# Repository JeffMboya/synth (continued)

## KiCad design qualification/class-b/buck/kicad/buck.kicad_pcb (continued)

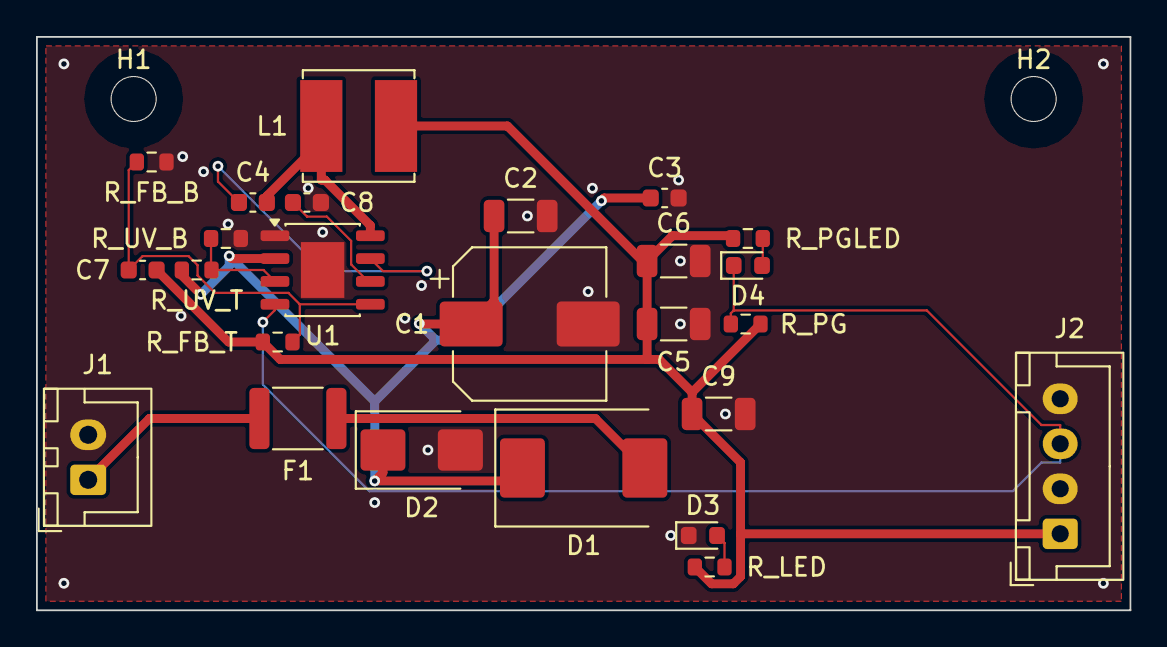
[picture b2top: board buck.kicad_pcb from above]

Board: 4 copper layers, 60.8 x 31.9 mm, 27 parts (0 on the bottom side), 13 nets.

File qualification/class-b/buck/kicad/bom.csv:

refdes,value,kind,description,kicad_symbol,kicad_footprint,lcsc_pn,mpn
C1,47uF,capacitor,"Honor Elec RVT1H470M0810, 47 uF 50 V +/-20 % 105 C SMD aluminium electrolytic, 8 mm diameter x 10.2 mm, polarised (pin 1 is +); JLCPCB C2895739",Device:C_Polarized,Capacitor_SMD:CP_Elec_8x10,,RVT1H470M0810
C2,10uF,capacitor,"Generic 1206 ceramic capacitor, any value",Device:C,Capacitor_SMD:C_1206_3216Metric,,
C3,220nF,capacitor,"Generic 0603 MLCC, X7R/X5R, any value",Device:C,Capacitor_SMD:C_0603_1608Metric,,
C4,100nF,capacitor,"Generic 0603 MLCC, X7R/X5R, any value",Device:C,Capacitor_SMD:C_0603_1608Metric,,
C5,22uF,capacitor,"Generic 1206 ceramic capacitor, any value",Device:C,Capacitor_SMD:C_1206_3216Metric,,
C6,22uF,capacitor,"Generic 1206 ceramic capacitor, any value",Device:C,Capacitor_SMD:C_1206_3216Metric,,
C7,56pF,capacitor,"Generic 0603 MLCC, X7R/X5R, any value",Device:C,Capacitor_SMD:C_0603_1608Metric,,
C8,1uF,capacitor,"Generic 0603 MLCC, X7R/X5R, any value",Device:C,Capacitor_SMD:C_0603_1608Metric,,
C9,22uF,capacitor,"Generic 1206 ceramic capacitor, any value",Device:C,Capacitor_SMD:C_1206_3216Metric,,
D1,SS36,diode,"Vishay SS36 60 V 3 A Schottky rectifier, SMC (DO-214AB), for reverse-polarity blocking",Diode:SS36,Diode_SMD:D_SMC,,SS36
D2,SMBJ30A,diode,"Vishay SMBJ30A 600 W unidirectional TVS, SMB (DO-214AA). max_voltage_v is the 30 V standoff VWM, not a clamp or abs max: VBR 33.3-36.8 V at 1 mA, VC 48.4 V at 12.4 A",Device:D_Zener,Diode_SMD:D_SMB,,SMBJ30A
D3,PWR,led,"Lite-On LTST-C190KGKT green AlInGaP LED, 0603, Vf 1.9 to 2.4V at 20mA",Device:LED,LED_SMD:LED_0603_1608Metric,,LTST-C190KGKT
D4,PG FAULT,led,"Lite-On LTST-C190KGKT green AlInGaP LED, 0603, Vf 1.9 to 2.4V at 20mA",Device:LED,LED_SMD:LED_0603_1608Metric,,LTST-C190KGKT
F1,1.1A_PTC,fuse,"Bourns MF-MSMF110/33X resettable PTC fuse, 1812. max_current_ma is Ihold 1.1 A at 23 C (0.63 A at 70 C, 0.50 A at 85 C); Itrip 2.2 A, Vmax 33 V",Device:Polyfuse,Fuse:Fuse_1812_4532Metric,,MF-MSMF110/33X
H1,M2.5,mounting_hole,M2.5 non-plated mounting hole (NPTH) for a board corner,Mechanical:MountingHole,MountingHole:MountingHole_2.5mm,,
H2,M2.5,mounting_hole,M2.5 non-plated mounting hole (NPTH) for a board corner,Mechanical:MountingHole,MountingHole:MountingHole_2.5mm,,
J1,24V_IN,connector,"JST XH 2.5 mm pitch 2-pin vertical header B2B-XH-A, 250 V / 3 A per JST XH sheet",Connector_Generic:Conn_01x02,Connector_JST:JST_XH_B2B-XH-A_1x02_P2.50mm_Vertical,,B2B-XH-A
J2,3V3_OUT,connector,"JST XH 2.5 mm pitch 4-pin vertical header B4B-XH-A, 250 V / 3 A per JST XH sheet",Connector_Generic:Conn_01x04,Connector_JST:JST_XH_B4B-XH-A_1x04_P2.50mm_Vertical,,B4B-XH-A
L1,6.8uH,inductor,"Bourns SRN6045TA-6R8M 6.8 uH semi-shielded power inductor, 6.0 x 6.0 mm. Datasheet typ: Isat 5.7 A (L drops 30%), Irms 3.6 A (max_current_ma is Irms), DCR 34 mOhm +-20%",Device:L,Inductor_SMD:L_Bourns_SRN6045TA,,SRN6045TA-6R8M
R_FB_B,43.2k,resistor,"Generic 0603 thick-film resistor, any value",Device:R_US,Resistor_SMD:R_0603_1608Metric,,
R_FB_T,100k,resistor,"Generic 0603 thick-film resistor, any value",Device:R_US,Resistor_SMD:R_0603_1608Metric,,
R_LED,470,resistor,"Generic 0603 thick-film resistor, any value",Device:R_US,Resistor_SMD:R_0603_1608Metric,,
R_PG,100k,resistor,"Generic 0603 thick-film resistor, any value",Device:R_US,Resistor_SMD:R_0603_1608Metric,,
R_PGLED,470,resistor,"Generic 0603 thick-film resistor, any value",Device:R_US,Resistor_SMD:R_0603_1608Metric,,
R_UV_B,100k,resistor,"Generic 0603 thick-film resistor, any value",Device:R_US,Resistor_SMD:R_0603_1608Metric,,
R_UV_T,1.37M,resistor,"Generic 0603 thick-film resistor, any value",Device:R_US,Resistor_SMD:R_0603_1608Metric,,
U1,LMR33640ADDA,regulator,"TI LMR33640 3.8-36 V input, 4 A synchronous step-down converter, 400 kHz, internal compensation, HSOIC-8 (DDA) with exposed thermal pad and open-drain power-good. VFB 1.0 V; VIN abs max 38 V",Regulator_Switching:LMR33640ADDA,Package_SO:HSOP-8-1EP_3.9x4.9mm_P1.27mm_EP2.41x3.1mm,,LMR33640ADDA

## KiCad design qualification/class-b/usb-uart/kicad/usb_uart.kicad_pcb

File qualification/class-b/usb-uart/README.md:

# USB-C dual UART + RS-485 adapter (SYN-66)

Status: design, placement and a FreeRouting route that passes Synth's release gate. The routed PCB, KiCad project and reports are in this PR. Not fabricated, not tested on hardware.
Do not call it proven or clean. The list of what is unchecked is at the bottom.

## What it is

- One USB-C port, one WCH CH342F (two UARTs).
- UART1 goes to pin headers as TTL (J2: GND, TXD1, RXD1; J3: DTR1, RTS1, CTS1).
- UART0 drives a TI THVD1450D RS-485 transceiver. Header J4: A, B, GND.
- DTR0/TNOW0 switches the transceiver direction. R_TNOW (4.7k to GND) puts UART0 in the CH342 half-duplex mode.
- Protection: PRTR5V0U2X on D+/D-, PTVS6V0S1UR on VBUS, CC1 and CC2. A 3.3 V LDO (LP5907) feeds the +3V3 rail.
- Four M2.5 mounting holes (H1 to H4), pinned in the placement sidecar: two at the top corners, two on the left and right edges at mid-height. The bottom corners are taken by the header row. Screw size and standoff height are not chosen.
- Source: `usb_uart.synth`. Sidecar: `usb_uart.placement.layout.toml` (board mm). The schematic has no sidecar: the compiler lays it out, one region per group.

## VIO jumper (J_VIO)

VIO is the I/O rail of both UARTs, the reset pin and the RS-485 chip. It is always 3.3 V or 5 V.
The THVD1450 needs 3 V or more, so 1.8 V and target-powered VIO were dropped.

| Jumper | VIO | Notes |
| --- | --- | --- |
| pins 1-2 | 3.3 V (LP5907) | default choice |
| pins 2-3 | 5 V (VBUS) | |
| none | off | CH342F stays in reset (VIO under 0.8 to 1.15 V), no enumeration. VIO LED is off. |

- VIO is not on J2 or J3, so a target cannot back-feed it. Do not wire anything to J_VIO pin 2.
- Forgotten jumper: the board only looks dead, and the VIO LED shows it.
- Not harmless with a powered target: a target driving RXD1 or CTS1 with VIO off goes past the CH342F limit of VIO+0.5 V.
  R5 and R6 (1k) limit the current to about 2.6 mA (3.3 V target) or 4.3 mA (5 V). The datasheet gives no clamp rating. Add the jumper first.

## Unused CH342F pins

- RI0, RI1, DCD0, DCD1, DSR0, DSR1: R8 (10k) pulls them to VIO (inactive, active low).
- CTS0: R9 (10k) holds it low, so UART0 flow control cannot stall.
- RST: left open (internal pull-up). The datasheet says unused lines may be left open; they are tied anyway.
- CTS1 floats if J3 is unplugged. Datasheet gives no pull-up for it.
- Datasheet 5.3: a pull-down on DTR1 at power-on switches UART1 to half-duplex. A target that holds DTR1 low at power-up changes the mode.

## BOM

| Ref | Part | MPN | Datasheet (revision seen) |
| --- | --- | --- | --- |
| U1 | WCH USB dual UART | CH342F | https://www.wch-ic.com/downloads/CH342DS1_PDF.html, V1E (file id 295, dated 2022-01-27) |
| U3 | TI RS-485 transceiver | THVD1450D | https://www.ti.com/lit/ds/symlink/thvd1450.pdf, SLLSEY3E (May 2018, rev May 2019) |
| U2 | TI 3.3 V LDO | LP5907MFX-3.3 | https://www.ti.com/lit/ds/symlink/lp5907.pdf, SNVS798Q (rev Jul 2025) |
| D1 | Nexperia USB ESD | PRTR5V0U2X | https://assets.nexperia.com/documents/data-sheet/PRTR5V0U2X.pdf, dated 1 Apr 2023 |
| D2, D5, D6 | Nexperia TVS 6 V | PTVS6V0S1UR | https://assets.nexperia.com/documents/data-sheet/PTVSXS1UR_SER.pdf, dated 1 Dec 2025 |
| D3 | Lite-On green LED | LTST-C190KGKT | https://optoelectronics.liteon.com/upload/download/DS22-2000-074/LTST-C190KGKT.PDF, revision not checked (site not reachable) |
| D4, D7 | Lite-On red LED | LTST-C190KRKT | https://optoelectronics.liteon.com/upload/download/DS-22-99-0151/LTST-C190KRKT.PDF, revision not checked (site not reachable) |
| J1 | USB-C receptacle | TYPE-C-31-M-12 | none in the registry, not checked |
| J2, J3, J4, J_VIO | 2.54 mm headers | generic 1x3 | none |
| C2, C3 | 2.2 uF X7R 0603 | generic | none |
| C4, C5, C6, C7 | 100 nF X7R 0603 | generic | none |
| R1, R2 | 5.1k | generic | none |
| R3, R4, R7 | 470 | generic | none |
| R5, R6 | 1k | generic | none |
| R8, R9 | 10k | generic | none |
| R_TNOW | 4.7k 1% | generic | none |
| R_TERM | 120 ohm 1% | generic | none |

Checked by me against the manufacturer file in this work: CH342F, THVD1450D, LP5907 (revision line only), the two Nexperia parts (revision line only).
The Nexperia and LP5907 electrical numbers were not re-read.

## Placement and routing (this commit)

Status: compact placement done and routed with FreeRouting. The route passes Synth's release gate; it is not reviewed or fabricated.

- Two copper layers: signals on F.Cu and B.Cu, a GND pour on both. The route uses no inner layer because the board has none; the previous revision was four layers with two inner GND planes that carried no routing.
- Outline: 40.99 x 32.23 mm as routed. The four M2.5 holes are at x 5.5 and 39.6 mm, y 3.0 and 21.0 mm, with a 2.2 mm board-feature rim. The header courtyards at y 29.9 mm set the 32.23 mm height. This is 3.5 mm shorter than the previous 35.73 mm compact layout and 7.5 mm shorter than the 39.73 mm committed board.
- Board-feature rim: Synth gives a mounting hole, test point or fiducial a fixed 2.2 mm rim in the fitted outline. With this sidecar the rim does not decide the outline: the holes are not the outermost parts, and the export gives the same outline with the rim set to 0. It matters if a hole is moved to the edge, where the tight 1.5 mm fit would otherwise cut it and split the F.Cu GND pour. `tests/usb_uart_board.rs` checks that every hole keeps at least 1.5 mm of room to Edge.Cuts on the exported board. The exporter sets `island_removal_mode 0`, dropping copper islands that touch no pad. KiCad lists a GND zone against itself when two fill islands that reach pads are not joined; Synth's gate now blocks on that. The previous revision had exactly this split.
- Every part has a position in `usb_uart.placement.layout.toml`. J1 sits flush on the top edge. J_VIO, J2, J3 and J4 sit at y 29.9 mm. J_VIO, J2, J3 and J4 are at x 7.36, 16.46, 26.0 and 35.1 mm. J3 and J4 each moved 1 mm left of their previous 27.0 and 36.1 mm: at the previous spot the GND pour split into two islands (C4 pin 2, J2 pin 1, D3 pin 1 and one via were cut off) and, with current KiCad and FreeRouting here, DTR1 was left unrouted. The 9.1 mm spacing between J3 and J4 keeps their 8.62 mm courtyards apart. The bottom parts sit at y 23.6 and 25.8 mm. R1 and R2 use the top corners; R3 moved to x 14.5 mm to clear H3.
- No courtyard overlaps. J1 courtyard to top edge: 0.01 mm. That is the 0.5 mm courtyard margin reaching the edge: the shell front face sits 0.50 mm inside Edge.Cuts. The HRO drawing states no overhang limit, so only the enclosure cutout fit is left to check.
- Pad-edge gap to the target pad on the same net:

| Part | Target | Gap mm |
| --- | --- | --- |
| C4 (VDD5) | U1 pin 7 | 0.97 |
| C5 (V3) | U1 pin 6 | 1.14 |
| C6 (VIO) | U1 pin 5 | 0.99 |
| C7 (VCC) | U3 pin 8 | 0.99 |
| C2 (LDO in) | U2 VBUS pins | 0.99 |
| C3 (LDO out) | U2 pin 5 | 0.99 |
| D1 D+ / D- | J1 D+ / D- pads | 1.76 / 1.69 |
| D2 (VBUS TVS) | J1 VBUS pad | 2.34 |
| D5 (CC1 TVS) | J1 CC1 pad | 1.95 |
| D6 (CC2 TVS) | J1 CC2 pad | 1.60 |

- D2 is over 2 mm: four protection parts do not fit side by side under the 7 mm of J1 pads any closer.
- R1 and R2 are in the top corners; the remaining passives are placed by hand. The DRC checks their courtyards, not placement quality.

Routing (FreeRouting 2.4.1, `router: "freerouting"`, `allow_via_in_pad: true`), with the Synth sources at `08b917b` (`source_revision` in `reports/release.json`):
- Result: routed. `release.json` has `release_ready` true and `routing.state` "routed", with no open net. `kicad-cli pcb drc --severity-all --refill-zones`: 0 errors, 0 warnings and no `unconnected_items`. Synth's gate no longer accepts a GND zone that KiCad lists against itself, and the delivered board has none. pcbnew's connectivity puts every GND pad and via in one cluster, so the pour is connected. (The earlier revision's 36 library-link warnings came from a run without the KiCad libraries.)
- 273 track segments, 43 vias, 515.4 mm of copper.
- The routed board is 40.99 x 32.23 mm.
- FreeRouting's escape analysis flags J1 and U1 (0.5 mm pitch) as the packages where neither a fabrication-floor via nor a minimum track fits between adjacent pads, and suggests 4 layers. The route still completes, with its only via-in-pad at U1 pin 25.
- J3 is at x 26.0 mm and J4 at x 35.1 mm in the sidecar. Small placement changes change FreeRouting's result: shifts of 0.5 mm in J3 and J4 left DTR1, TNOW0 or +3V3 unrouted, and a 0.5 mm shift of C4 left USB_DN open. The same inputs gave the same board on three runs.
- Via-in-pad at the U1 exposed pad (pin 25), at (23.900, 17.300) mm. The fab must fill and cap it. JLCPCB has not been asked.
- Signal-integrity pass: 23 warnings, none blocking. All 23 are layer changes with no ground return via within 1.53 mm, so the return current has to jump between the F.Cu and B.Cu pours.
- The USB pair is not coupled. Measured on the committed board: full-speed part, pair on F.Cu only with no via (the 23 layer-change warnings are on other nets), DP 38.63 mm and DN 13.52 mm so 25.11 mm of skew (about 0.2 percent of a full-speed bit), and 91.4 percent of the length over solid B.Cu GND fill. These are my measurements, not an independent review; see `qualification.json`. FreeRouting does not couple the pair. On two layers at 1.6 mm, a 90 ohm differential pair needs about 1.18 mm traces, so the pair has no impedance target and no controlled-impedance geometry (the previous four-layer revision declared 90 ohm but never verified it).
- No part has been reviewed (`reviewer_state` is false for every part in `release.json`).
- Silkscreen: the D7, J4, J_VIO and U1 reference labels are placed by hand in the sidecar. `kicad-cli pcb drc` reports no silkscreen warning.
- TX LEDs: D4 and D7 take their current from VIO through R4 and R7 and sink it into TXD0 and TXD1, so they are dark while a line idles and lit on the low bits. Each draws about 3 mA at 3.3 V and 6.6 mA at 5 V from the CH342 TXD pin (an estimate from a 1.9 V forward drop; the CH342 output drive was not checked at 5 V).

## Committed artifacts

- `kicad/`: the routed PCB, schematic, symbol library, project, DRC rules and BOM.
- `reports/`: `release.json`, the delivered DRC, ERC and the routing record. Its `production_status` and `release_ready` fields only mean the route passed Synth's router and DRC gates, and its `gate_scope` field says so. Neither is a fabrication approval.
- `qualification.json`: the qualification gate. `qualified` stays false until every review gate in it is true.
- `dfm/`: the gerber zip, CPL and screenshots from the JLCPCB quote and DFM flow on 2026-10-27 (no order placed). It is partial: see `jlcpcb_dfm` in `qualification.json`.
- `images/`: 3D top and angled, top and bottom copper, and the schematic. The 3D and copper pictures were rendered with `kicad-cli pcb render` and `pcb export pdf` from the committed board.
- `dfm/`: regenerated Gerbers, drill and CPL for this board. The JLCPCB screenshots there are from the previous revision and were not redone; see `qualification.json`.
- `SHA256SUMS`: hashes of the artifacts above.

The reports are as the commands produce them, except that the absolute paths of the machine that produced them were cut to repo-relative ones (`out/...` is the export directory) and `source_revision` in `reports/release.json` was added by hand. The release report is the CLI's own format (`synth.release.v1`), which differs from the MCP report in the earlier revision.

The committed board came from the CLI commands below (FreeRouting engine, via-in-pad allowed).

## Commands (use an empty `XDG_DATA_HOME` so a user registry cannot shadow parts)

```
export XDG_DATA_HOME=$(mktemp -d)
scripts/setup-routing-engines.sh --freerouting-only
synth validate qualification/class-b/usb-uart/usb_uart.synth
synth export-kicad qualification/class-b/usb-uart/usb_uart.synth --out /tmp/usb_uart --router free-routing --krt-allow-via-in-pad
kicad-cli pcb drc --severity-all --refill-zones --format json /tmp/usb_uart/usb_uart.kicad_pcb -o /tmp/usb_uart/usb_uart-drc.json
kicad-cli sch erc --severity-all --format json /tmp/usb_uart/usb_uart.kicad_sch -o /tmp/usb_uart/usb_uart-erc.json
(cd qualification/class-b/usb-uart && sha256sum -c SHA256SUMS)
```

A route that passes the gate is `usb_uart.kicad_pcb`; a failed one stays in `usb_uart.freerouting.kicad_pcb`. The unrouted placement is `usb_uart.synth.kicad_pcb`.
Current Synth main defaults the MCP export to KiCadRoutingTools; this board was routed with FreeRouting. Add `--best-of --kicad-routing-tools-repo <dir> --kicad-routing-tools-python <python>` to the CLI to try KiCadRoutingTools.

## Known limits and gaps

- Schematic: an earlier exporter bug drew the CH342F wires 1.27 mm short of its pins. With commit 9592ad5 (PR #104) applied, the netlist shows U1 connected (only RST and RTS0 left open). Without that fix, KiCad sees every U1 pin as unconnected.
- Schematic look: the compiler's own layout, not tuned by hand. See `images/schematic.png`.
- KiCad schematic ERC: 0 errors and 1 warning (label_multiple_wires); a run without the KiCad libraries also reports 80 lib_symbol_issues and 36 footprint_link_issues. VIO arrives only through J_VIO, so the exporter puts a PWR_FLAG on it.
- Validate still warns: E-SYNTH-POWER-004 x2 (VBUS and GND load-to-capacitor ratio, a count heuristic), E-SYNTH-SCHEM-005 x2 (CH342F bridge junction fan-out), W-SYNTH-ANOMALY-001, W-SYNTH-SUPPLY-002 x8, W-SYNTH-PART-UNVERIFIED x9.
- No VBUS bulk capacitor, no fuse, no reverse or inrush protection.
- R_TERM (120 ohm across A/B) is always connected. The registry has no 2-pin header (`header_1x2`) for a jumper.
- RS-485: no bias resistors (the THVD1450 has idle, open and short bus failsafe built in, per SLLSEY3E). No surge or TVS on A/B: only the on-chip +/-18 kV IEC contact ESD. TI shows an external circuit for 1 kV surge. No common-mode choke.
- No silkscreen text support in Synth: header labels (GND/TXD1/RXD1 and so on) exist only in the schematic.
- The route passes Synth's own gate but nobody has reviewed it, so the board is not ready to fabricate.
- Two-layer board with no declared stackup: the exporter writes the 1.6 mm default thickness. There is no controlled-impedance net, and the USB pair is not impedance-controlled.

## Not verified

- Lite-On LED numbers are second-hand (from PR #90); the Lite-On site was not reachable.
- CH342F datasheet: V1E is the newest I found on wch-ic.com. WCH's CH340 sheet was out of date once before, so a newer CH342 sheet may exist.
- Exposed pad: KiCad footprint 2.6 mm, supplier drawing 2.4 mm. Not reconciled.
- Parts availability, JLCPCB assembly, and the registry LCSC numbers were not checked.
- Nothing was powered or tested.

Reproducibility: on 2026-10-27 three runs of the commands above (FreeRouting 2.4.1 on Java 25, KiCad 10.0.7, Synth at the commit in `reports/release.json` `source_revision`, two of them with an empty `XDG_DATA_HOME`) gave a byte-identical `kicad_pcb`; the schematic is unchanged. The FreeRouting jar and JRE are untracked and come from `tools/` after `scripts/setup-routing-engines.sh --freerouting-only`. The router is sensitive: the previous placement did not route on this setup, so a different FreeRouting or KiCad version may need a different placement. I did not try another machine. `qualification.json` lists the input and output hashes.

The ERC findings and the silkscreen and edge-clearance items are dispositioned one by one in `qualification.json`. The 0.01 mm J1 courtyard clearance is the courtyard margin only (shell face 0.50 mm inside the edge, per the HRO drawing); independent mechanical approval of the cutout fit is still open; the silkscreen warnings are fixed with label overrides in the sidecar. The exported schematic used to tie RXD1_MCU to MODEM_IDLE through a name label that sat on a crossing wire; the exporter now keeps that label off other nets' wires, and the schematic and ERC report were regenerated.

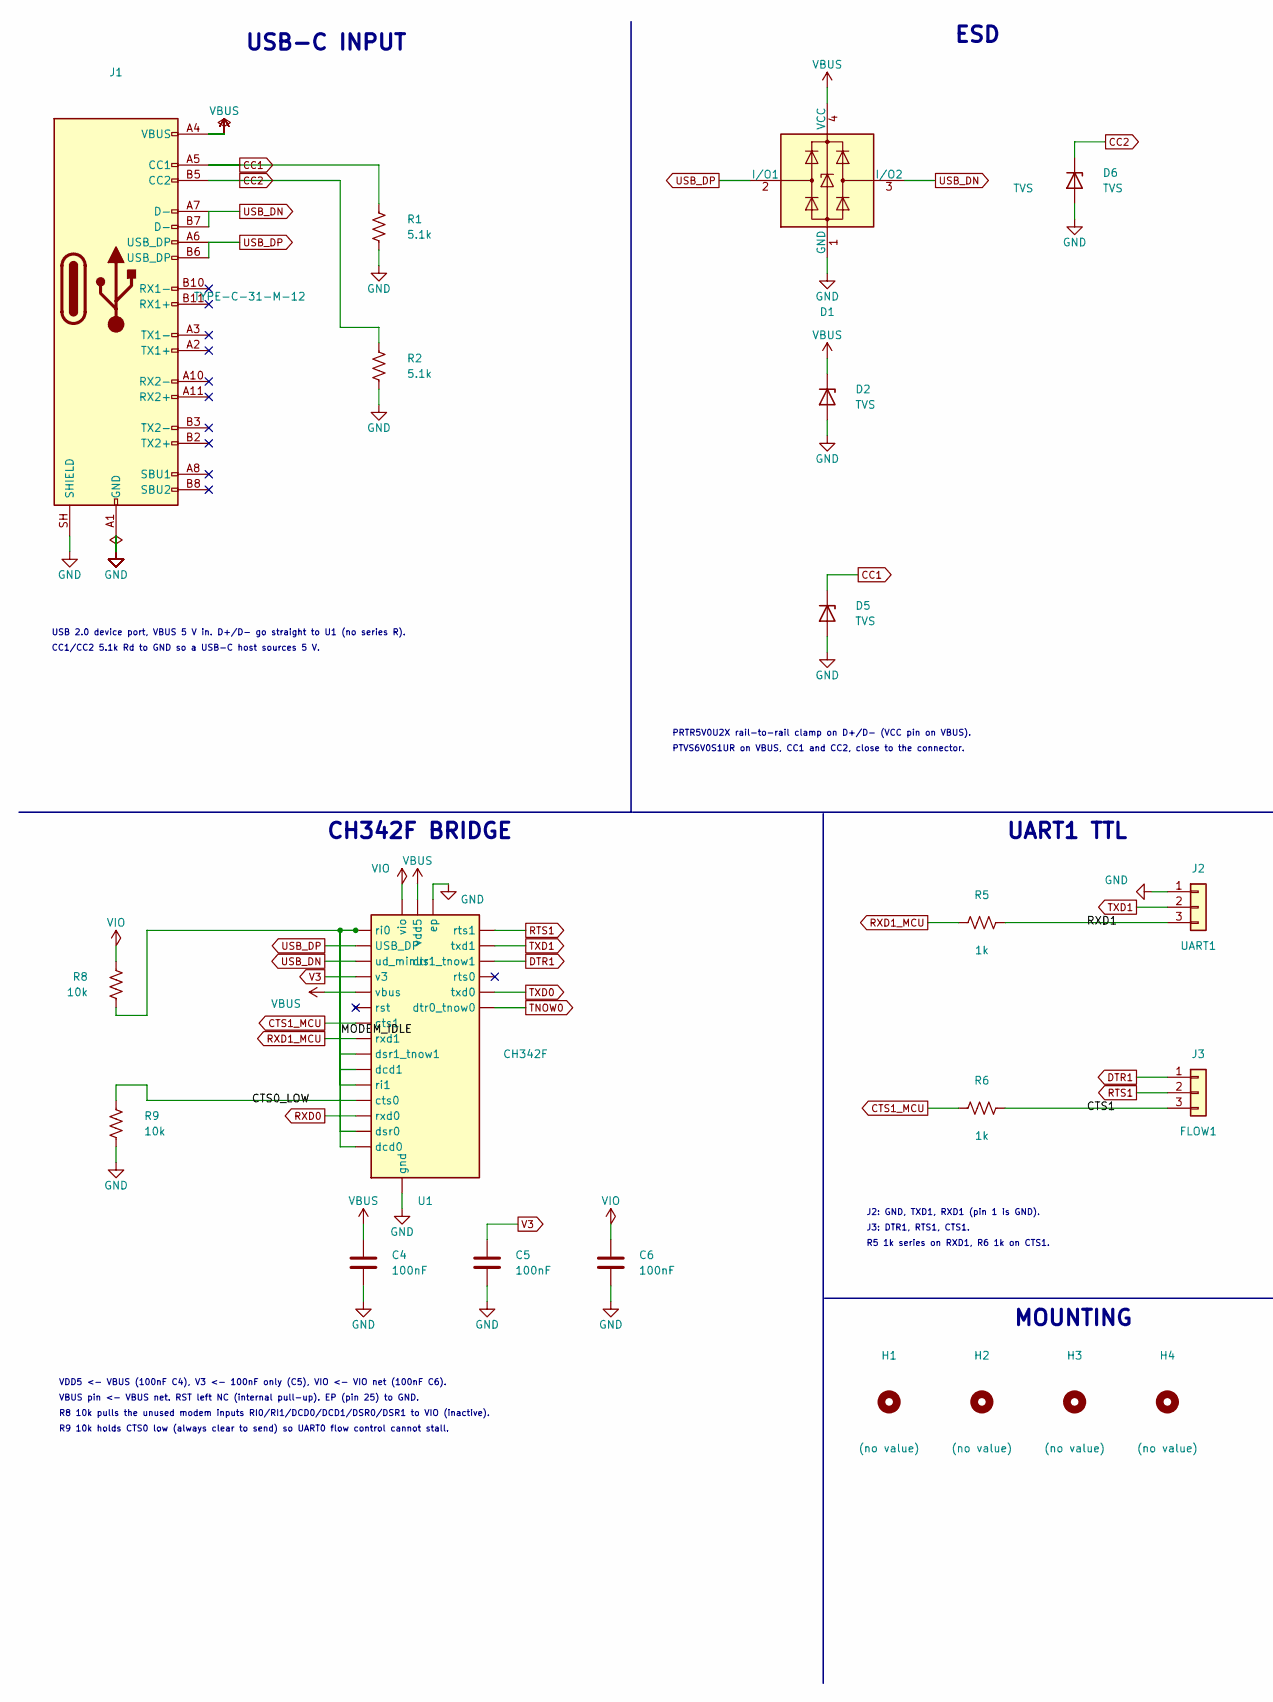
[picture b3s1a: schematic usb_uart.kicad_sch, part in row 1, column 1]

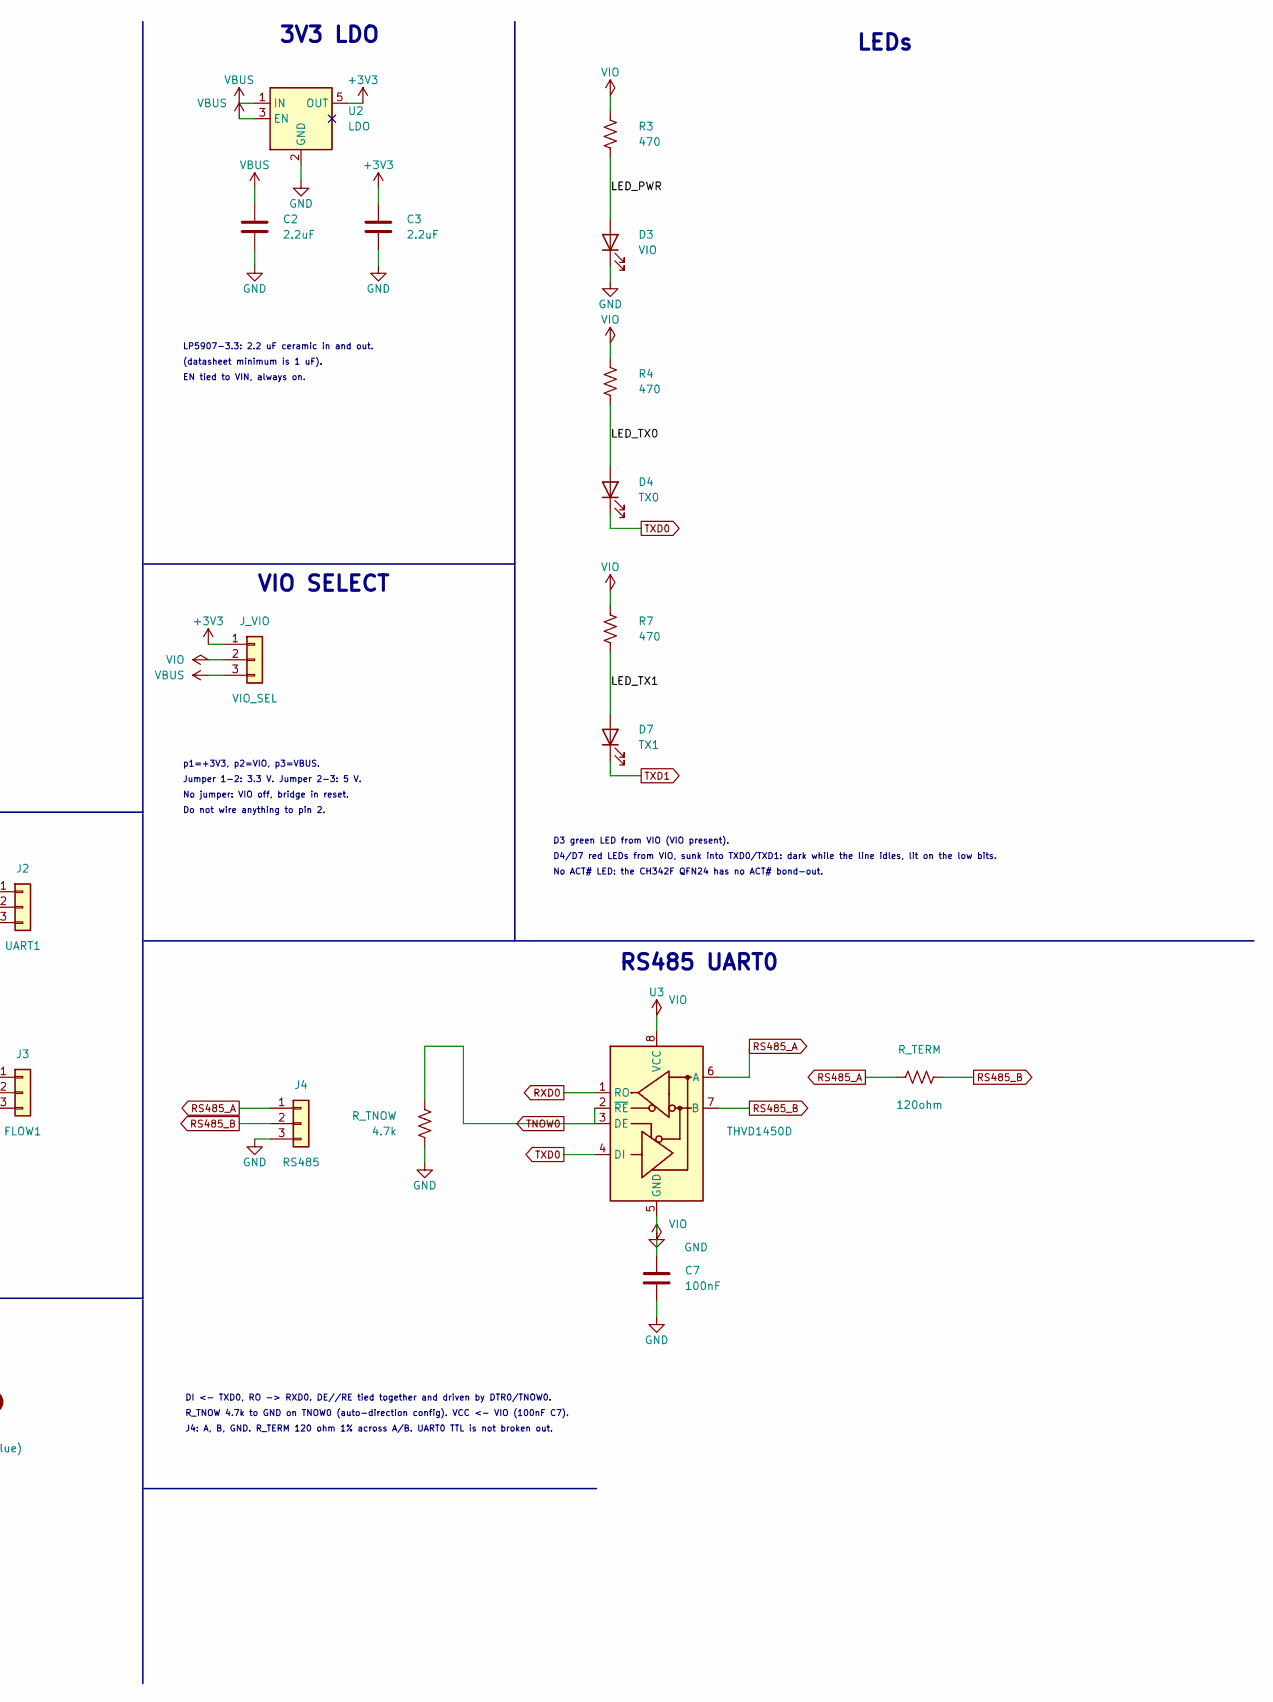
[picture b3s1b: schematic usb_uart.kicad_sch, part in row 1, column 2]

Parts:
C2, C3: 2.2uF; C_0603_1608Metric; Voltage 16V
C4, C5, C6, C7: 100nF; C_0603_1608Metric; Voltage 16V
D1: TVS; SOT-143; MPN PRTR5V0U2X
D2, D5, D6: TVS; Nexperia_CFP3_SOD-123W; MPN PTVS6V0S1UR
D3: VIO; LED_0603_1608Metric; MPN LTST-C190KGKT
D4: TX0; LED_0603_1608Metric; MPN LTST-C190KRKT
D7: TX1; LED_0603_1608Metric; MPN LTST-C190KRKT
H1, H2, H3, H4: (no value); MountingHole_2.5mm
J1: TYPE-C-31-M-12; USB_C_Receptacle_HRO_TYPE-C-31-M-12; MPN TYPE-C-31-M-12; LCSC C165948
J2: UART1; PinHeader_1x03_P2.54mm_Vertical
J3: FLOW1; PinHeader_1x03_P2.54mm_Vertical
J4: RS485; PinHeader_1x03_P2.54mm_Vertical
J_VIO: VIO_SEL; PinHeader_1x03_P2.54mm_Vertical
R1, R2: 5.1k; R_0603_1608Metric
R3, R4, R7: 470; R_0603_1608Metric
R5, R6: 1k; R_0603_1608Metric
R8, R9: 10k; R_0603_1608Metric
R_TERM: 120ohm; R_0603_1608Metric; Tolerance 1%
R_TNOW: 4.7k; R_0603_1608Metric; Tolerance 1%
U1: CH342F; QFN-24-1EP_4x4mm_P0.5mm_EP2.6x2.6mm; MPN CH342F; LCSC C2841530
U2: LDO; SOT-23-5; MPN LP5907MFX-3.3; LCSC C83437
U3: THVD1450D; SOIC-8_3.9x4.9mm_P1.27mm; MPN THVD1450D; LCSC C2671361

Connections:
+3V3: C3.1, J_VIO.1, U2.5 (OUT)
CC1: D5.1 (K), J1.A5 (CC1), R1.1
CC2: D6.1 (K), J1.B5 (CC2), R2.1
CTS0_LOW: R9.1, U1.18 (cts0)
CTS1: J3.3, R6.2
CTS1_MCU: R6.1, U1.10 (cts1)
DTR1: J3.1, U1.15 (dtr1_tnow1)
GND: C2.2, C3.2, C4.2, C5.2, C6.2, C7.2, D1.1 (GND), D2.2 (A), D3.1 (K), D5.2 (A), D6.2 (A), J1.A1 (GND), J1.A12 (GND), J1.B1 (GND), J1.B12 (GND), J1.SH (SHIELD), J2.1, J4.3, R1.2, R2.2, R9.2, R_TNOW.2, U1.2 (gnd), U1.25 (ep), U2.2 (GND), U3.5 (GND)
LED_PWR: D3.2 (A), R3.2
LED_TX0: D4.2 (A), R4.2
LED_TX1: D7.2 (A), R7.2
MODEM_IDLE: R8.2, U1.1 (ri0), U1.14 (dsr1_tnow1), U1.16 (dcd1), U1.17 (ri1), U1.22 (dsr0), U1.24 (dcd0)
RS485_A: J4.1, R_TERM.1, U3.6 (A)
RS485_B: J4.2, R_TERM.2, U3.7 (B)
RTS1: J3.2, U1.11 (rts1)
RXD0: U1.20 (rxd0), U3.1 (RO)
RXD1: J2.3, R5.2
RXD1_MCU: R5.1, U1.12 (rxd1)
TNOW0: R_TNOW.1, U1.23 (dtr0_tnow0), U3.2 (~RE), U3.3 (DE)
TXD0: D4.1 (K), U1.21 (txd0), U3.4 (DI)
TXD1: D7.1 (K), J2.2, U1.13 (txd1)
USB_DN: D1.3 (I/O2), J1.A7 (D-), J1.B7 (D-), U1.4 (ud_minus)
USB_DP: D1.2 (I/O1), J1.A6 (D+), J1.B6 (D+), U1.3 (ud_plus)
V3: C5.1, U1.6 (v3)
VBUS: C2.1, C4.1, D1.4 (VCC), D2.1 (K), J1.A4 (VBUS), J1.A9 (VBUS), J1.B4 (VBUS), J1.B9 (VBUS), J_VIO.3, U1.7 (vdd5), U1.8 (vbus), U2.1 (IN), U2.3 (EN)
VIO: C6.1, C7.1, J_VIO.2, R3.1, R4.1, R7.1, R8.1, U1.5 (vio), U3.8 (VCC)

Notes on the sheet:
MOUNTING
USB-C INPUT
ESD
3V3 LDO
CH342F BRIDGE
VIO SELECT
UART1 TTL
RS485 UART0
LEDs
USB 2.0 device port, VBUS 5 V in. D+/D- go straight to U1 (no series R).
CC1/CC2 5.1k Rd to GND so a USB-C host sources 5 V.
PRTR5V0U2X rail-to-rail clamp on D+/D- (VCC pin on VBUS).
PTVS6V0S1UR on VBUS, CC1 and CC2, close to the connector.
LP5907-3.3: 2.2 uF ceramic in and out.
(datasheet minimum is 1 uF).
EN tied to VIN, always on.
VDD5 <- VBUS (100nF C4), V3 <- 100nF only (C5), VIO <- VIO net (100nF C6).
VBUS pin <- VBUS net. RST left NC (internal pull-up). EP (pin 25) to GND.
R8 10k pulls the unused modem inputs RI0/RI1/DCD0/DCD1/DSR0/DSR1 to VIO (inactive).
R9 10k holds CTS0 low (always clear to send) so UART0 flow control cannot stall.
p1=+3V3, p2=VIO, p3=VBUS.
Jumper 1-2: 3.3 V. Jumper 2-3: 5 V.
No jumper: VIO off, bridge in reset.
Do not wire anything to pin 2.
J2: GND, TXD1, RXD1 (pin 1 is GND).
J3: DTR1, RTS1, CTS1.
R5 1k series on RXD1, R6 1k on CTS1.
DI <- TXD0, RO -> RXD0. DE//RE tied together and driven by DTR0/TNOW0.
R_TNOW 4.7k to GND on TNOW0 (auto-direction config). VCC <- VIO (100nF C7).
J4: A, B, GND. R_TERM 120 ohm 1% across A/B. UART0 TTL is not broken out.
D3 green LED from VIO (VIO present).
D4/D7 red LEDs from VIO, sunk into TXD0/TXD1: dark while the line idles, lit on the low bits.
No ACT# LED: the CH342F QFN24 has no ACT# bond-out.

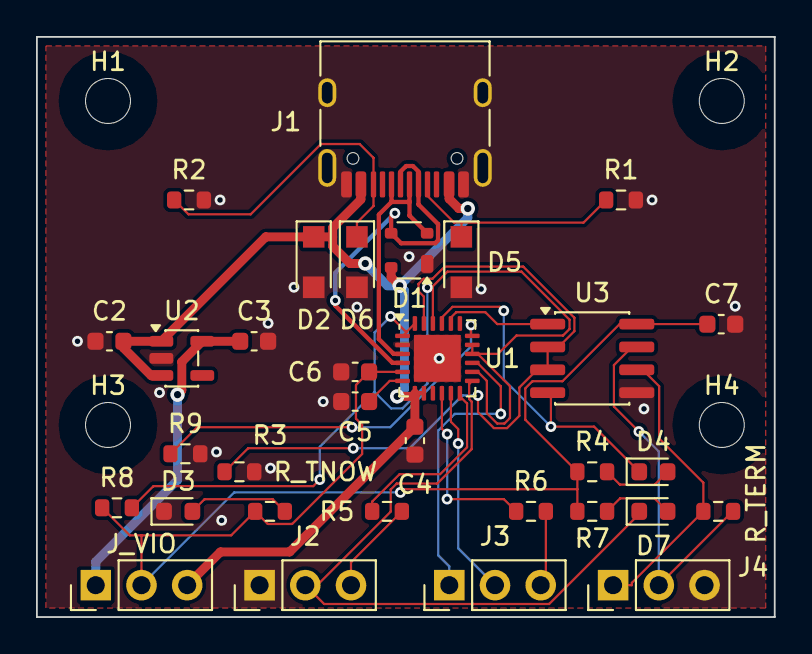
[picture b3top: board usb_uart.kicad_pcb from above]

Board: 2 copper layers, 41.0 x 32.2 mm, 36 parts (0 on the bottom side), 26 nets.

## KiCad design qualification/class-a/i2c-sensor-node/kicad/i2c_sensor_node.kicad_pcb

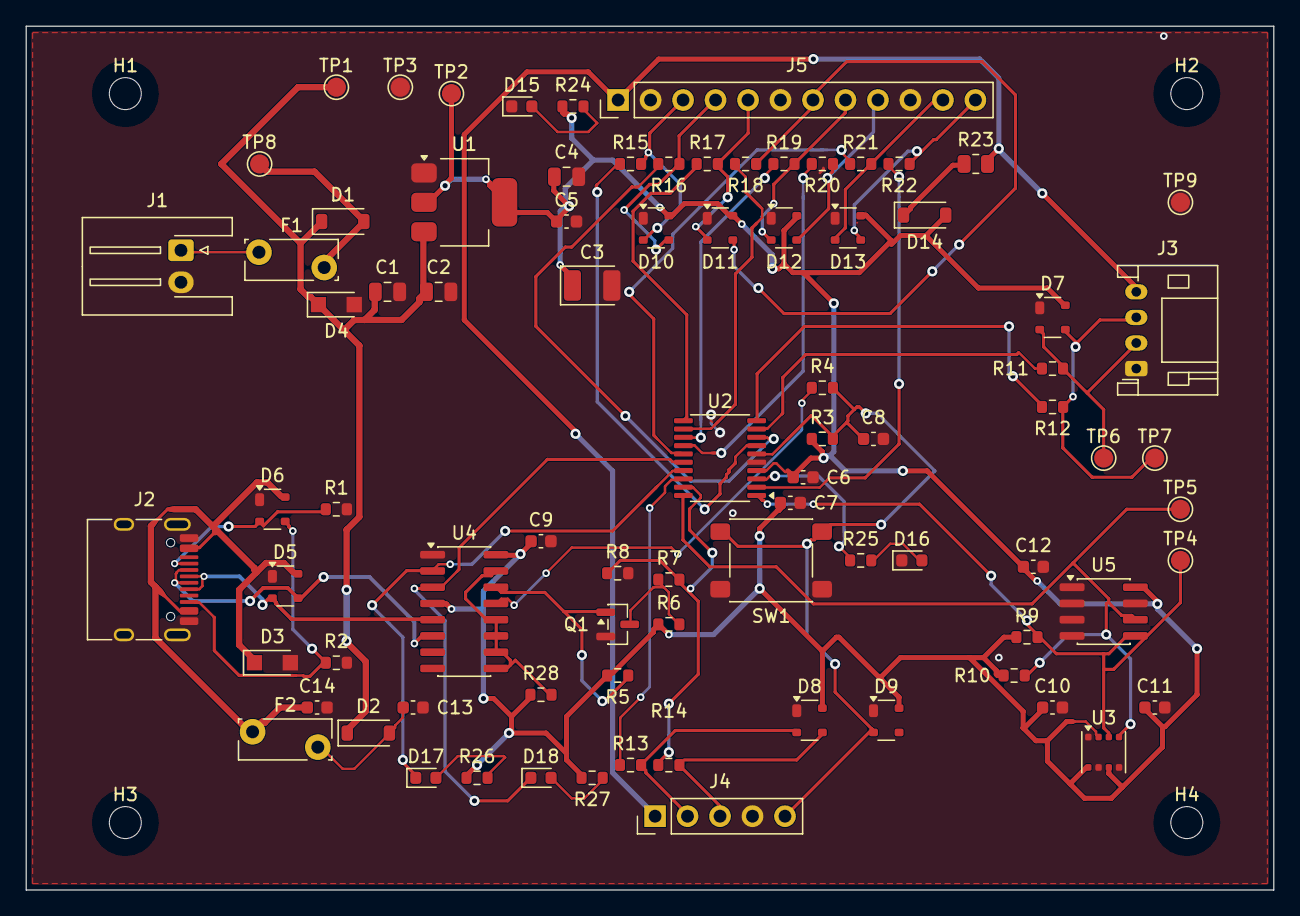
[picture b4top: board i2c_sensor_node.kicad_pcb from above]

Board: 2 copper layers, 97.5 x 67.5 mm, 87 parts (0 on the bottom side), 51 nets.

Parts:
C1, C2, C4: 10uF; C_0805_2012Metric
C3: 47uF; CP_EIA-3528-21_Kemet-B
C5, C6, C8, C9, C10, C11, C12, C14: 100nF; C_0603_1608Metric
C7, C13: 4.7uF; C_0603_1608Metric
D1, D2, D14: 1N5819; D_SOD-123
D3, D4: PTVS6V0S1UR; Nexperia_CFP3_SOD-123W
D5, D6, D7, D8, D9, D10, D11, D12, D13: PRTR5V0U2X; SOT-143
D15, D18: GREEN; LED_0603_1608Metric
D16: AMBER; LED_0603_1608Metric
D17: RED; LED_0603_1608Metric
F1, F2: 0.5A hold; Fuse_Bourns_MF-RG300
H1, H2, H3, H4: (no value); MountingHole_2.5mm
J1: JST S2B-XH-A-1; JST_XH_S2B-XH-A-1_1x02_P2.50mm_Horizontal
J2: TYPE-C-31-M-12; USB_C_Receptacle_HRO_TYPE-C-31-M-12
J3: JST S4B-PH-K-S; JST_PH_S4B-PH-K_1x04_P2.00mm_Horizontal
J4: SWD; PinHeader_1x05_P2.54mm_Vertical
J5: GPIO; PinHeader_1x12_P2.54mm_Vertical
Q1: IRLML6244; SOT-23
R1, R2: 5.1k; R_0603_1608Metric
R3, R6, R28: 10k; R_0603_1608Metric
R4, R7, R12, R26, R27: 1k; R_0603_1608Metric
R5, R8: 100k; R_0603_1608Metric
R9, R10: 4.7k; R_0603_1608Metric
R11, R15, R16, R17, R18, R19, R20, R21, R22: 330; R_0603_1608Metric
R13, R14: 100; R_0603_1608Metric
R23: 100; R_0805_2012Metric
R24, R25: 680; R_0603_1608Metric
SW1: RESET; SW_SPST_PTS645Sx43SMTR92
TP1: +5V_PROT; TestPoint_Pad_D1.5mm
TP2: +3V3; TestPoint_Pad_D1.5mm
TP3, TP9: GND; TestPoint_Pad_D1.5mm
TP4: I2C_SDA; TestPoint_Pad_D1.5mm
TP5: I2C_SCL; TestPoint_Pad_D1.5mm
TP6: UART_TX; TestPoint_Pad_D1.5mm
TP7: UART_RX; TestPoint_Pad_D1.5mm
TP8: VIN_FUSED; TestPoint_Pad_D1.5mm
U1: AMS1117-3.3; SOT-223-3_TabPin2
U2: STM32G030F6P6; TSSOP-20_4.4x6.5mm_P0.65mm
U3: BME680; Bosch_LGA-8_3x3mm_P0.8mm_ClockwisePinNumbering
U4: CH340C; SOIC-16_3.9x9.9mm_P1.27mm
U5: 24LC256-I/SN; SOIC-8_3.9x4.9mm_P1.27mm

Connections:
3V3_REF: J3.4, J4.1, J5.1, R23.2
+3V3: C3.1, C4.1, C5.1, C6.1, C7.1, C9.1, C10.1, C11.1, C12.1, D7.4, D8.4, D9.4, D10.4, D11.4, D12.4, D13.4, D14.2, R3.1, R5.1, R6.1, R9.1, R10.1, R24.1, R26.1, R27.1, R28.1, TP2.1, U1.2, U2.4, U3.2, U3.6, U3.8, U4.4, U4.16, U5.8
+5V_PROT: C1.1, C2.1, D1.1, D2.1, D4.1, TP1.1, U1.3
BOOT_DRV: Q1.3, R6.2, R7.1
BRIDGE_RXD: D18.1, U2.16, U4.3
BRIDGE_TXD: D17.1, U2.17, U4.2
CH340_STRAP: R28.2, U4.9, U4.10, U4.11, U4.12, U4.15
DTR_N: R4.1, U4.13
GND: C1.2, C2.2, C3.2, C4.2, C5.2, C6.2, C7.2, C8.2, C9.2, C10.2, C11.2, C12.2, C13.2, C14.2, D3.2, D4.2, D5.1, D6.1, D7.1, D8.1, D9.1, D10.1, D11.1, D12.1, D13.1, D15.1, D16.1, J1.2, J2.A1, J2.A12, J2.B1, J2.B12, J2.SH, J3.1, J4.4, J5.2, J5.6, J5.10, Q1.2, R1.2, R2.2, R8.2, SW1.2, TP3.1, TP9.1, U1.1, U2.5, U3.1, U3.5, U3.7, U4.1, U5.1, U5.2, U5.3, U5.4, U5.7
GPIO_PA0: D10.2, J5.3, R15.2
GPIO_PA0_MCU: R15.1, U2.7
GPIO_PA1: D10.3, J5.4, R16.2
GPIO_PA1_MCU: R16.1, U2.8
GPIO_PA4: D11.2, J5.5, R17.2
GPIO_PA4_MCU: R17.1, U2.11
GPIO_PA5: D11.3, J5.7, R18.2
GPIO_PA5_MCU: R18.1, U2.12
GPIO_PA6: D12.2, J5.8, R19.2
GPIO_PA6_MCU: R19.1, U2.13
GPIO_PA7: D12.3, J5.9, R20.2
GPIO_PA7_MCU: R20.1, U2.14
GPIO_PB0: D13.2, J5.11, R21.2
GPIO_PB0_MCU: R21.1, U2.15
GPIO_PB9: D13.3, J5.12, R22.2
GPIO_PB9_MCU: R22.1, U2.2
I2C_SCL: R10.2, TP5.1, U2.20, U3.4, U5.6
I2C_SDA: R9.2, TP4.1, U2.1, U3.3, U5.5
LED_PWR: D15.2, R24.2
LED_RXA: D18.2, R27.2
LED_STATUS: R25.1, U2.3
LED_STATUS_A: D16.2, R25.2
LED_TXA: D17.2, R26.2
NRST: C8.1, D9.2, J4.5, R3.2, R4.2, SW1.1, U2.6
REF_D: D14.1, R23.1
RTS_N: Q1.1, R5.2, U4.14
SWCLK: D8.3, J4.3, R14.2
SWCLK_MCU: R7.2, R8.1, R14.1, U2.19
SWDIO: D8.2, J4.2, R13.2
SWDIO_MCU: R13.1, U2.18
U2_RX: R12.1, U2.10
U2_TX: R11.1, U2.9
UART_RX: D7.3, J3.3, R12.2, TP7.1
UART_TX: D7.2, J3.2, R11.2, TP6.1
USB_CC1: D6.2, J2.A5, R1.1
USB_CC2: D6.3, J2.B5, R2.1
USB_DN: D5.3, J2.A7, J2.B7, U4.6
USB_DP: D5.2, J2.A6, J2.B6, U4.5
VBUS_FUSED: C13.1, D2.2, F2.2
VBUS_USB: C14.1, D3.1, D5.4, D6.4, F2.1, J2.A4, J2.A9, J2.B4, J2.B9
VIN_5V_FUSED: D1.2, F1.2, TP8.1
VIN_5V_RAW: F1.1, J1.1

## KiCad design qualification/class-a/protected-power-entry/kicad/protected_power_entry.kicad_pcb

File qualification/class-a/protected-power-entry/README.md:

# Protected Power Entry Board

Protected power entry board with reverse-polarity and over-current protection.

## Features
- Q1 reverse-polarity PFET
- D1 SMAJ15A TVS (over-voltage protection)
- MP2307 5V buck converter
- TPS22918 load switch
- AMS1117 3.3V LDO

## Status
- Validation: 0 errors, 56 warnings
- Routing: 2 unconnected nets (+12V_PROT, +3V3) - needs fix

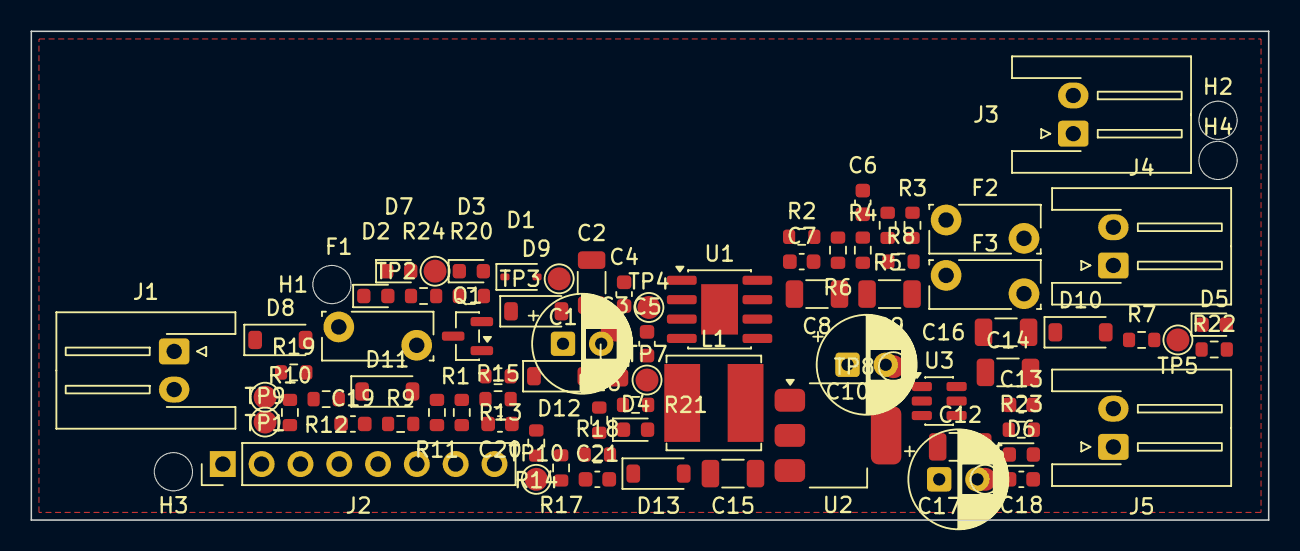
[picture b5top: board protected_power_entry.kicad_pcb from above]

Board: 2 copper layers, 81.0 x 32.0 mm, 84 parts (0 on the bottom side), 34 nets, no tracks yet.

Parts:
C1, C10, C17: 100uF 25V; CP_Radial_D6.3mm_P2.50mm
C2, C3: 10uF 25V; C_1206_3216Metric
C4, C6, C18, C19, C20, C21: 100nF; C_0603_1608Metric
C5: 10nF; C_0603_1608Metric
C7, C13: 2.2nF; C_0603_1608Metric
C8, C9, C14: 22uF 10V; C_1206_3216Metric
C12, C15, C16: 10uF 10V; C_1206_3216Metric
D1: (no value); D_SOD-323
D2, D3, D6: (no value); LED_0603_1608Metric
D4: LTST-C190KGKT; LED_0603_1608Metric
D5: 0603-GREEN; LED_0603_1608Metric
D7: LTST-C190KRKT; LED_0603_1608Metric
D8: 1N5819HW-7-F; D_SOD-123
D9, D10: (no value); D_SOD-123
D11, D12, D13: BZT52C3V3; D_SOD-123
F1, F2, F3: (no value); Fuse_Bourns_MF-RG300
H1, H2, H3, H4: (no value); MountingHole_2.5mm
J1, J3, J4, J5: (no value); JST_XH_S2B-XH-A-1_1x02_P2.50mm_Horizontal
J2: M20-9990846; PinHeader_1x08_P2.54mm_Vertical
L1: SRN6045TA-100M; L_Bourns_SRN6045TA
Q1: (no value); SOT-23
R1: 47k; R_0603_1608Metric
R2, R4, R10, R13, R14, R16, R17: 10k; R_0603_1608Metric
R3: 44.2k; R_0603_1608Metric
R5, R7: 100k; R_0603_1608Metric
R6: 33k; R_0603_1608Metric
R8, R12, R15, R18, R21, R22: 1k; R_0603_1608Metric
R9: 100; R_0603_1608Metric
R11: 2k; R_0603_1608Metric
R19: 3k; R_0603_1608Metric
R20, R24: 3.3k; R_0603_1608Metric
R23: 470; R_0603_1608Metric
TP1, TP2, TP3, TP4, TP5, TP6, TP7, TP8, TP9, TP10: (no value); TestPoint_Pad_D1.5mm
U1: MP2307DN-LF-Z; SOIC-8-1EP_3.9x4.9mm_P1.27mm_EP2.41x3.3mm
U2: AMS1117-3.3; SOT-223-3_TabPin2
U3: TPS22918DBVR; SOT-23-6

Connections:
3V3_REF: J2.1, R9.2
+3V3: C16.1, C17.1, C18.1, J5.1, R9.1, R16.1, R23.1, TP6.1, U2.2
+5V: C8.1, C9.1, C10.1, C12.1, C15.1, F2.1, L1.2, R3.1, R13.1, R21.1, TP4.1, U2.3, U3.1
+5V_SW: C14.1, F3.1, R22.1, TP5.1, U3.5, U3.6
+12V_PROT: C1.1, C2.1, C3.1, C4.1, D1.1, D9.1, Q1.2, R5.1, R10.1, R20.1, TP3.1, U1.2
BUCK_BS: C5.1, U1.1
BUCK_COMP: R2.1, U1.6
BUCK_CRC: C7.1, R2.2
BUCK_EN: R5.2, R6.1, U1.7
BUCK_FB: R3.2, R4.1, U1.5
BUCK_SS: C6.1, U1.8
BUCK_SW: C5.2, L1.1, TP7.1, U1.3
EN_HDR: J2.3, R8.1
FLT_A: D7.2, R24.2
GND: C1.2, C2.2, C3.2, C4.2, C6.2, C7.2, C8.2, C9.2, C10.2, C12.2, C13.2, C14.2, C15.2, C16.2, C17.2, C18.2, C19.2, C20.2, C21.2, D1.2, D2.1, D3.1, D4.1, D5.1, D6.1, D10.2, D11.2, D12.2, D13.2, J1.2, J2.2, J2.4, J2.8, J3.2, J4.2, J5.2, R1.2, R4.2, R6.2, R7.2, R11.2, R14.2, R17.2, TP9.1, TP10.1, U1.4, U1.9, U2.1, U3.2
LED3V3_A: D6.2, R23.2
LED5SW_A: D5.2, R22.2
LED5_A: D4.2, R21.2
LED12_A: D3.2, R20.2
LED_IN_A: D8.2, R19.2
LED_IN_B: D2.2, D8.1
LOAD_EN: D10.1, R7.1, R8.2, TP8.1, U3.3
LS_CT: C13.1, U3.4
OUT_5V: F2.2, J3.1
OUT_5V_SW: F3.2, J4.1
PFET_GATE: D9.2, Q1.1, R1.1
S3_DIV: D13.1, R16.2, R17.1, R18.1
S5_DIV: D12.1, R13.2, R14.1, R15.1
S12_DIV: D11.1, R10.2, R11.1, R12.1
SENSE_3V3: C21.1, J2.7, R18.2
SENSE_5V: C20.1, J2.6, R15.2
SENSE_12V: C19.1, J2.5, R12.2
VIN_12V_FUSED: D7.1, F1.2, Q1.3, TP2.1
VIN_12V_RAW: F1.1, J1.1, R19.1, R24.1, TP1.1
